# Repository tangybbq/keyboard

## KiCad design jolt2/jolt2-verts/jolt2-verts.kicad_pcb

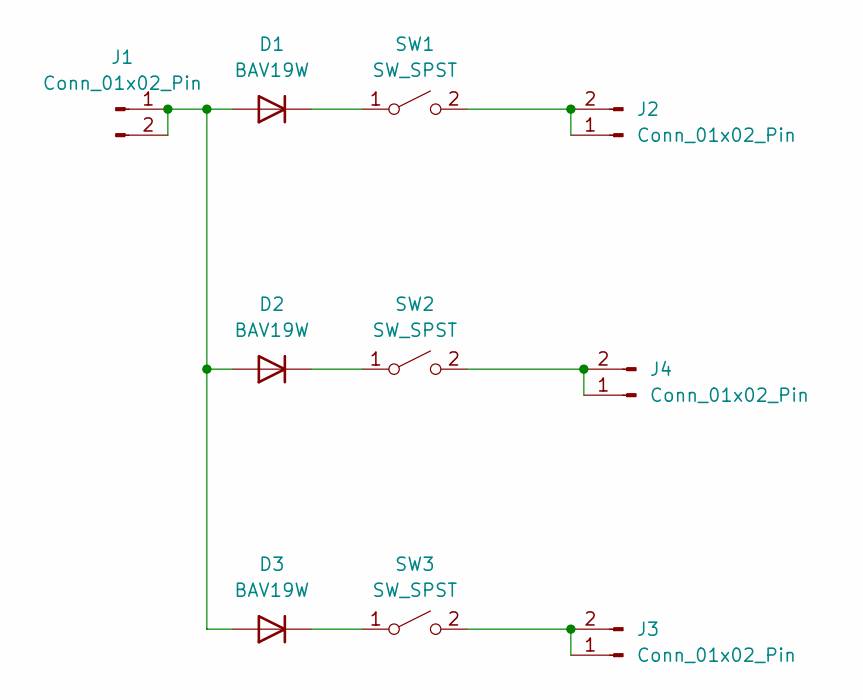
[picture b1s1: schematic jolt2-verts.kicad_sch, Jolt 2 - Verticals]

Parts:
D1, D2, D3: BAV19W; Nexperia_CFP3_SOD-123W
J1, J2, J3, J4: Conn_01x02_Pin; PinHeader_1x02_P2.54mm_Vertical
SW1, SW2, SW3: SW_SPST; Kailh_socket_PG1350

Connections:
unnamed: D1.2 (A), D2.2 (A), D3.2 (A), J1.1, J1.2
unnamed: D1.1 (K), SW1.1 (A)
unnamed: D2.1 (K), SW2.1 (A)
unnamed: D3.1 (K), SW3.1 (A)
unnamed: J2.1, J2.2, SW1.2 (B)
unnamed: J3.1, J3.2, SW3.2 (B)
unnamed: J4.1, J4.2, SW2.2 (B)

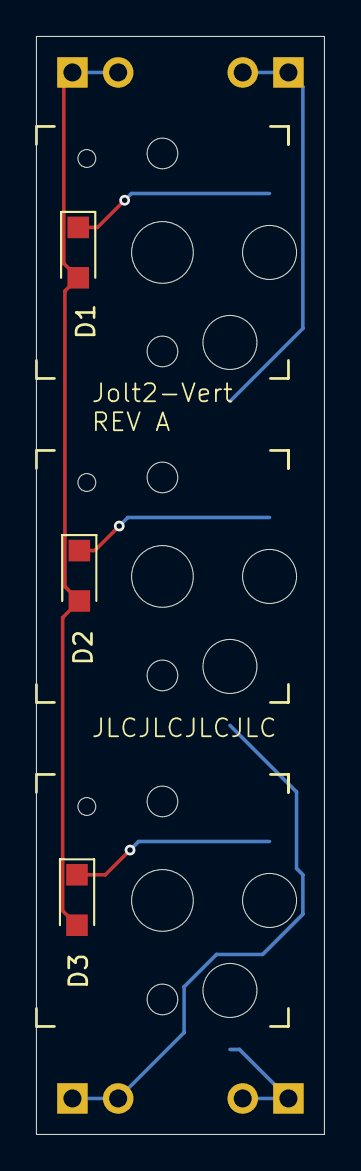
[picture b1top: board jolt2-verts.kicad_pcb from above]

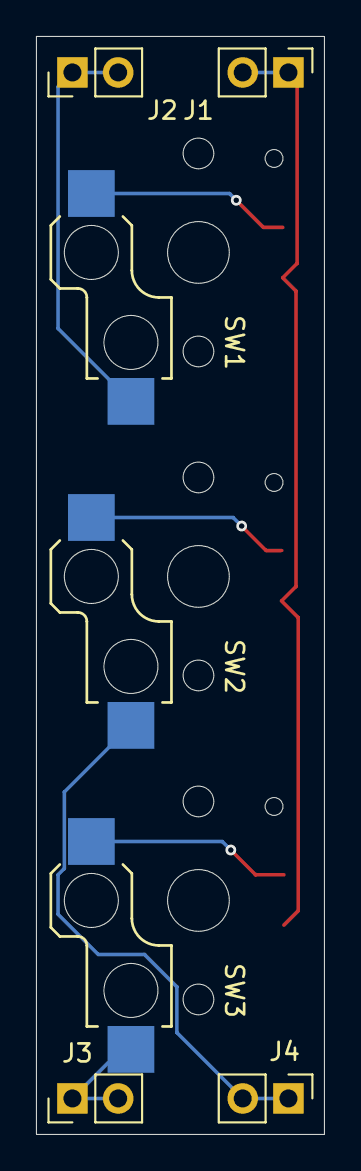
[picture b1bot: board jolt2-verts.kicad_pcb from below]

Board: 2 copper layers, 16.0 x 61.0 mm, 10 parts (4 on the bottom side), 7 nets.

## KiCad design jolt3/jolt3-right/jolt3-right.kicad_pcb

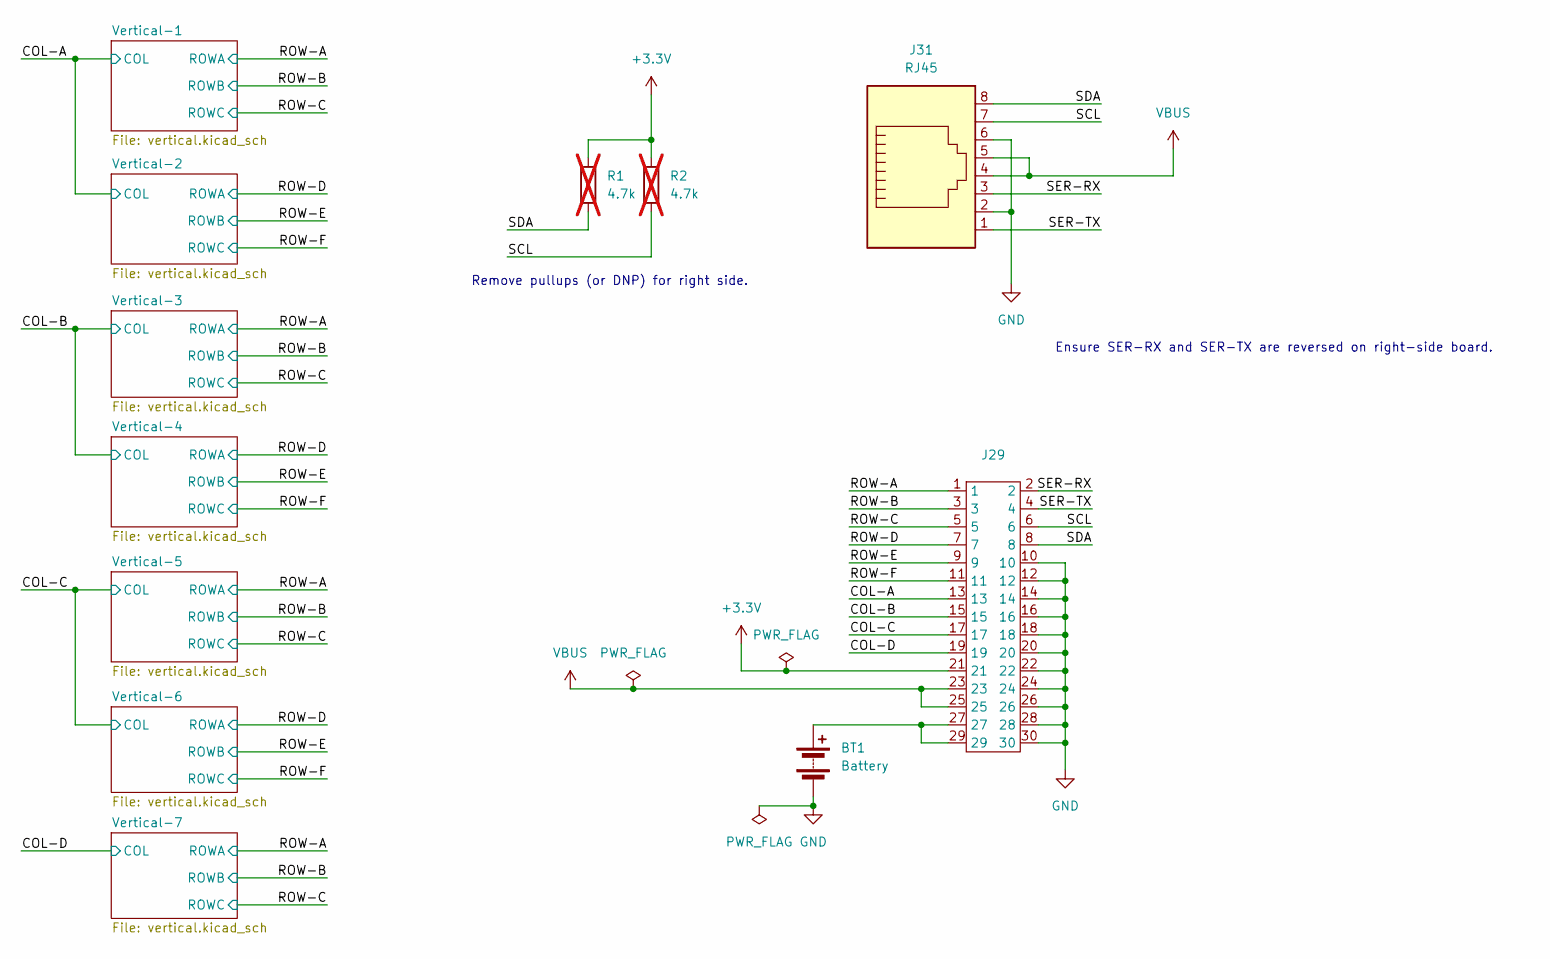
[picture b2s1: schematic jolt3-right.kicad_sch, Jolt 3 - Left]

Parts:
BT1: Battery; BAT-2xAA-SHELL-CASE-BOX
J29: df40c-2_0-30P-0_4v
J31: RJ45; RJ45_Amphenol_54602-x08_Horizontal
R1, R2: 4.7k; R_0603_1608Metric_Pad0.98x0.95mm_HandSolder; not fitted

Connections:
+3.3V: J29.21, R1.1, R2.1
/COL-A: J29.13; also elsewhere on the board
/COL-B: J29.15; also elsewhere on the board
/COL-C: J29.17; also elsewhere on the board
/COL-D: J29.19; also elsewhere on the board
/ROW-A: J29.1; also elsewhere on the board
/ROW-B: J29.3; also elsewhere on the board
/ROW-C: J29.5; also elsewhere on the board
/ROW-D: J29.7; also elsewhere on the board
/ROW-E: J29.9; also elsewhere on the board
/ROW-F: J29.11; also elsewhere on the board
/SCL: J29.6, J31.7, R2.2
/SDA: J29.8, J31.8, R1.2
/SER-RX: J29.2, J31.3
/SER-TX: J29.4, J31.1
GND: BT1.2 (-), J29.10, J29.12, J29.14, J29.16, J29.18, J29.20, J29.22, J29.24, J29.26, J29.28, J29.30, J31.2, J31.6
unnamed: BT1.1 (+), J29.27, J29.29
VBUS: J29.23, J29.25, J31.4, J31.5

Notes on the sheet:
Ensure SER-RX and SER-TX are reversed on right-side board.
Remove pullups (or DNP) for right side.

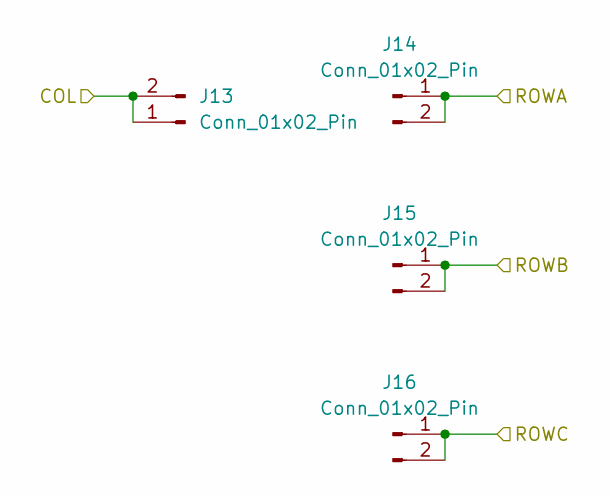
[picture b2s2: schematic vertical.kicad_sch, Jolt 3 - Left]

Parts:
J13, J14, J15, J16: Conn_01x02_Pin; PinHeader_1x02_P2.54mm_Vertical

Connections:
/COL-B: J13.1, J13.2; also elsewhere on the board
/ROW-D: J14.1, J14.2; also elsewhere on the board
/ROW-E: J15.1, J15.2; also elsewhere on the board
/ROW-F: J16.1, J16.2; also elsewhere on the board

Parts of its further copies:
J1, J2, J3, J4, J5, J6, J7, J8, J9, J10, J11, J12, J17, J18, J19, J20, J21, J22, J23, J24, J25, J26, J27, J28: Conn_01x02_Pin; PinHeader_1x02_P2.54mm_Vertical

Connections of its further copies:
/COL-A: J1.1, J1.2, J5.1, J5.2; also elsewhere on the board
/COL-B: J9.1, J9.2; also elsewhere on the board
/COL-C: J17.1, J17.2, J21.1, J21.2; also elsewhere on the board
/COL-D: J25.1, J25.2; also elsewhere on the board
/ROW-A: J2.1, J2.2, J10.1, J10.2, J18.1, J18.2, J26.1, J26.2; also elsewhere on the board
/ROW-B: J3.1, J3.2, J11.1, J11.2, J19.1, J19.2, J27.1, J27.2; also elsewhere on the board
/ROW-C: J4.1, J4.2, J12.1, J12.2, J20.1, J20.2, J28.1, J28.2; also elsewhere on the board
/ROW-D: J6.1, J6.2, J22.1, J22.2; also elsewhere on the board
/ROW-E: J7.1, J7.2, J23.1, J23.2; also elsewhere on the board
/ROW-F: J8.1, J8.2, J24.1, J24.2; also elsewhere on the board

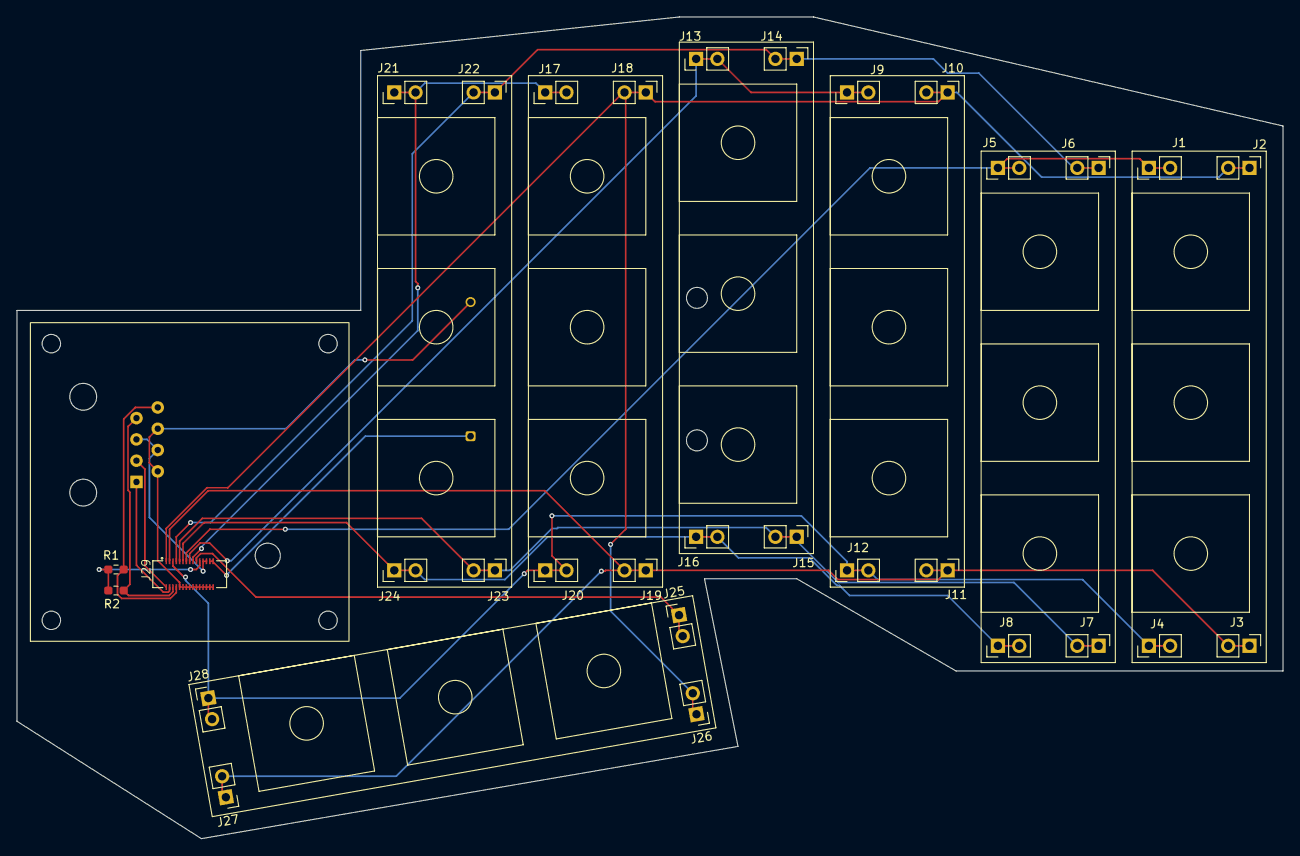
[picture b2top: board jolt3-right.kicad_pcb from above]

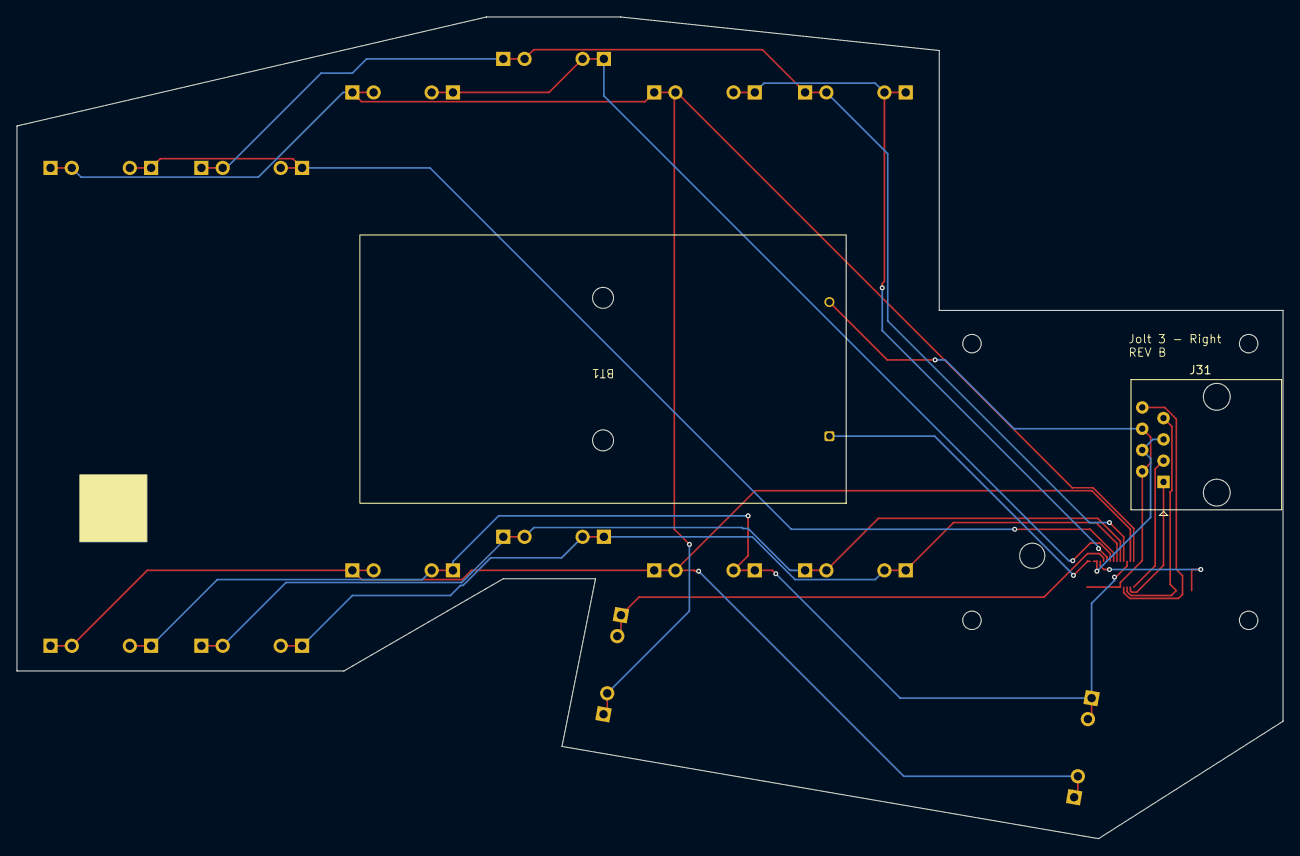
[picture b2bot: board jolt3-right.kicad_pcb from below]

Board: 2 copper layers, 151.0 x 98.0 mm, 33 parts (2 on the bottom side), 18 nets.

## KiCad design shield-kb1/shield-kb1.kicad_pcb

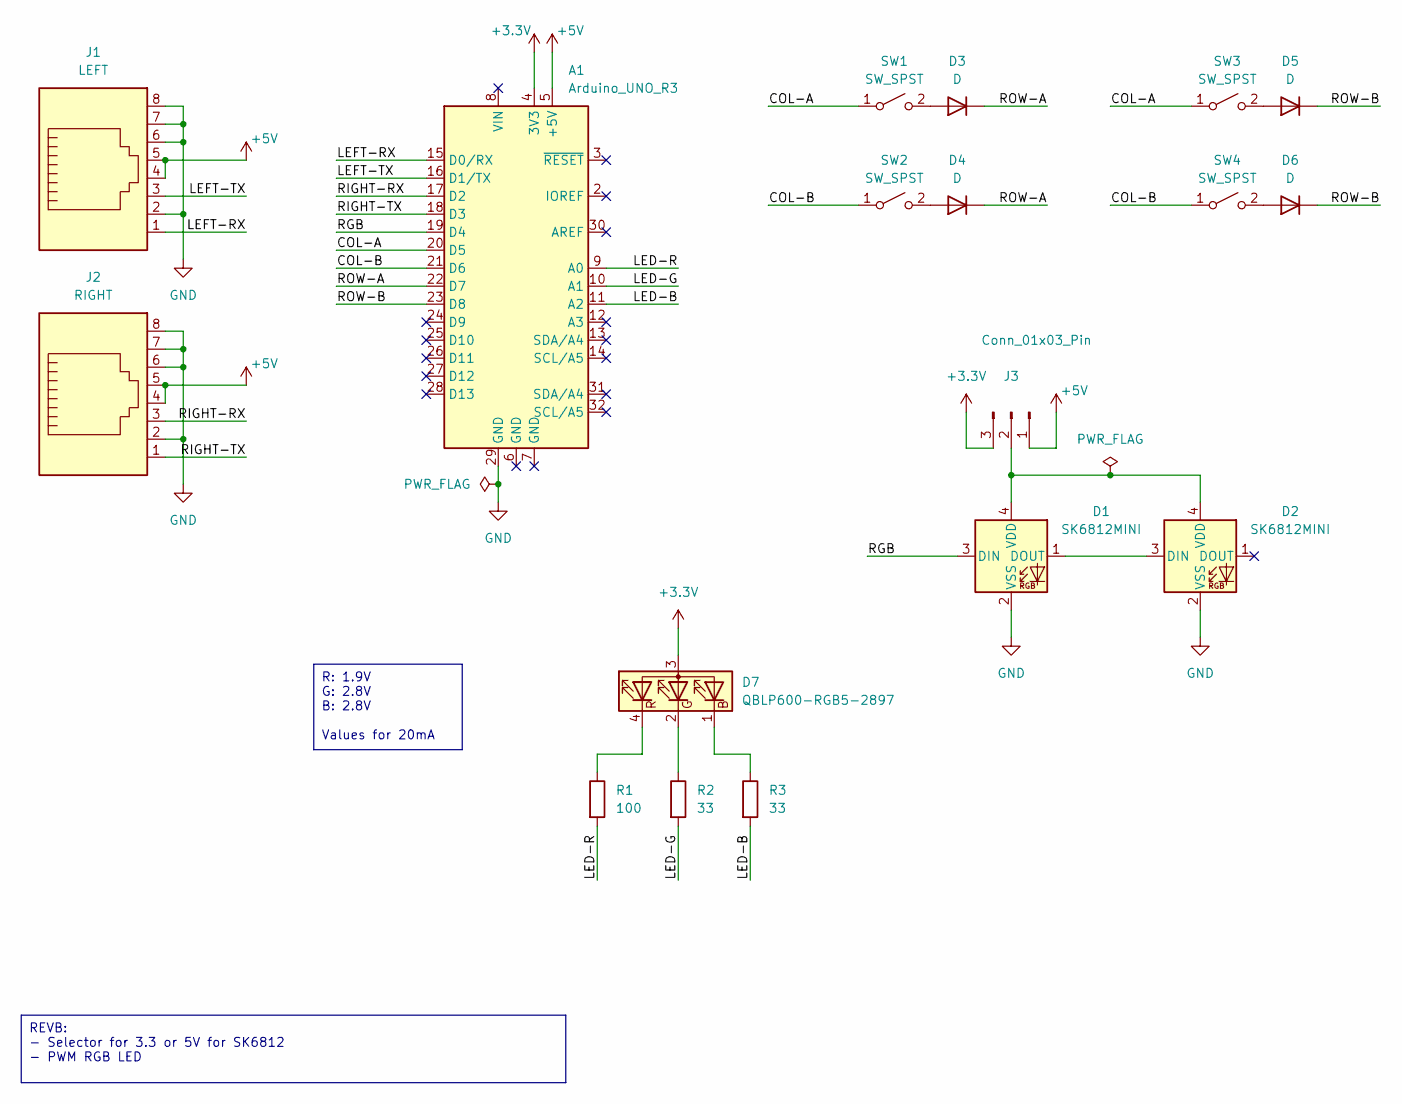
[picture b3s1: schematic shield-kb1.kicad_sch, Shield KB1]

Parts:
A1: Arduino_UNO_R3
D1, D2: SK6812MINI; LED_SK6812MINI_PLCC4_3.5x3.5mm_P1.75mm
D3, D4, D5, D6: D; Nexperia_CFP3_SOD-123W
D7: QBLP600-RGB5-2897
J1: LEFT; RJ45_Amphenol_54602-x08_Horizontal
J2: RIGHT; RJ45_Amphenol_54602-x08_Horizontal
J3: Conn_01x03_Pin; PinHeader_1x03_P2.54mm_Vertical
R1: 100; R_0603_1608Metric_Pad0.98x0.95mm_HandSolder
R2, R3: 33; R_0603_1608Metric_Pad0.98x0.95mm_HandSolder
SW1, SW2, SW3, SW4: SW_SPST; Kailh_socket_PG1350

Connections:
+3.3V: A1.4 (3V3), D7.3 (A), J3.3
+5V: A1.5 (+5V), J1.4, J1.5, J2.4, J2.5, J3.1
/COL-A: A1.20 (D5), SW1.1 (A), SW3.1 (A)
/COL-B: A1.21 (D6), SW2.1 (A), SW4.1 (A)
/LED-B: A1.11 (A2), R3.2
/LED-G: A1.10 (A1), R2.2
/LED-R: A1.9 (A0), R1.2
/LEFT-RX: A1.15 (D0/RX), J1.1
/LEFT-TX: A1.16 (D1/TX), J1.3
/RGB: A1.19 (D4), D1.3 (DIN)
/RIGHT-RX: A1.17 (D2), J2.3
/RIGHT-TX: A1.18 (D3), J2.1
/ROW-A: A1.22 (D7), D3.1 (K), D4.1 (K)
/ROW-B: A1.23 (D8), D5.1 (K), D6.1 (K)
GND: A1.29 (GND), D1.2 (VSS), D2.2 (VSS), J1.2, J1.6, J1.7, J1.8, J2.2, J2.6, J2.7, J2.8
unnamed: D1.1 (DOUT), D2.3 (DIN)
unnamed: D1.4 (VDD), D2.4 (VDD), J3.2
unnamed: D3.2 (A), SW1.2 (B)
unnamed: D4.2 (A), SW2.2 (B)
unnamed: D5.2 (A), SW3.2 (B)
unnamed: D6.2 (A), SW4.2 (B)
unnamed: D7.1 (BK), R3.1
unnamed: D7.2 (GK), R2.1
unnamed: D7.4 (RK), R1.1

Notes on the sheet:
REVB: - Selector for 3.3 or 5V for SK6812 - PWM RGB LED
R: 1.9V G: 2.8V B: 2.8V Values for 20mA

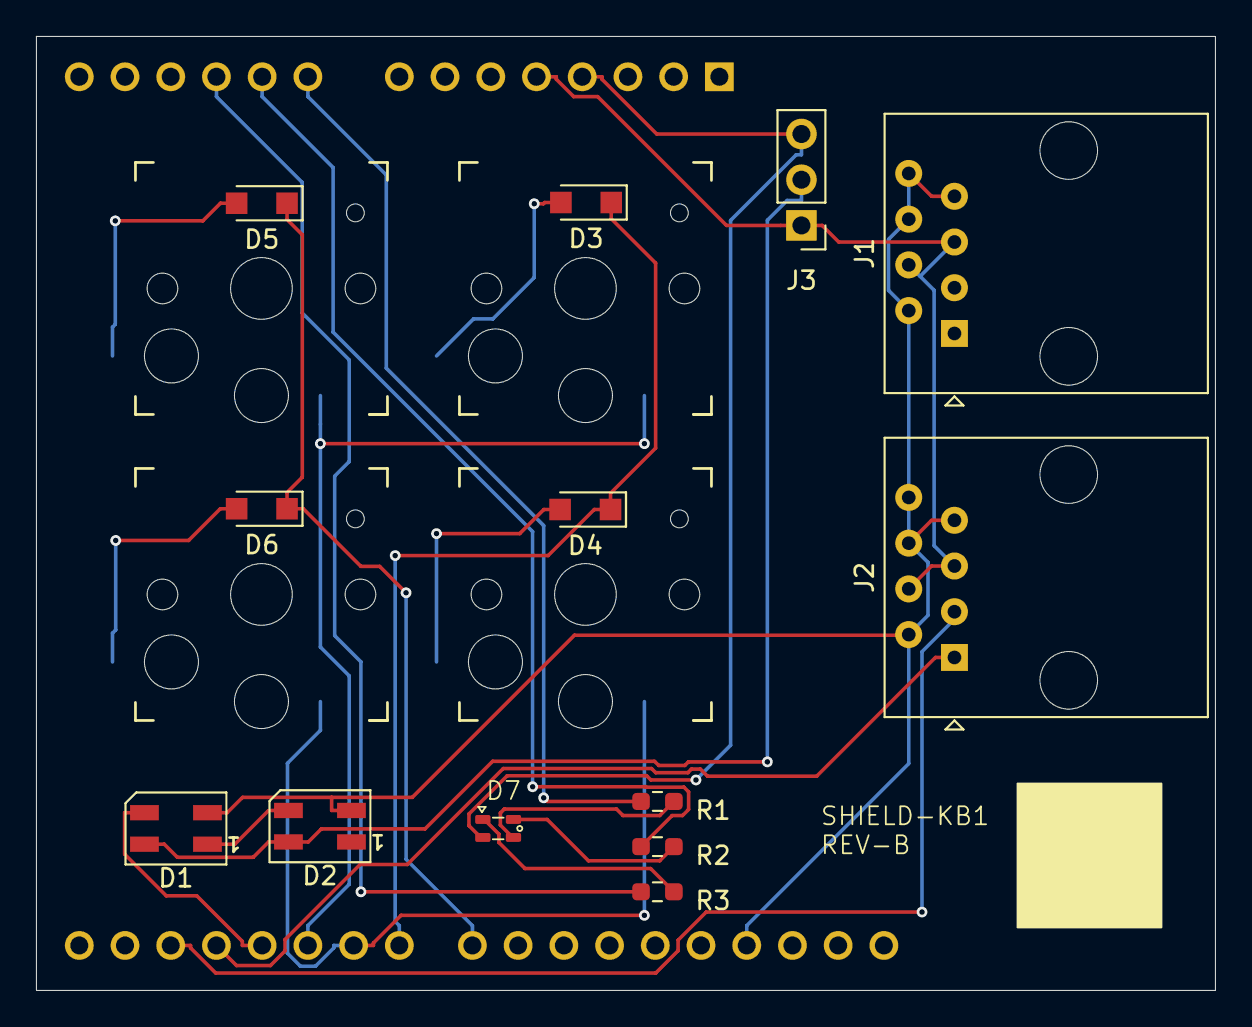
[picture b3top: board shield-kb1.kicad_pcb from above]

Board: 2 copper layers, 65.5 x 53.0 mm, 18 parts (1 on the bottom side), 24 nets.
